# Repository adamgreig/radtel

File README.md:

# RadTel

This is a simple radio telemetry module using an STM32F0 microcontroller and an 
Si4460 radio transceiver. The board is designed to be used as part of a KiCAD 
tutorial workshop demonstrating basic circuit design, schematic capture, and 
PCB layout.

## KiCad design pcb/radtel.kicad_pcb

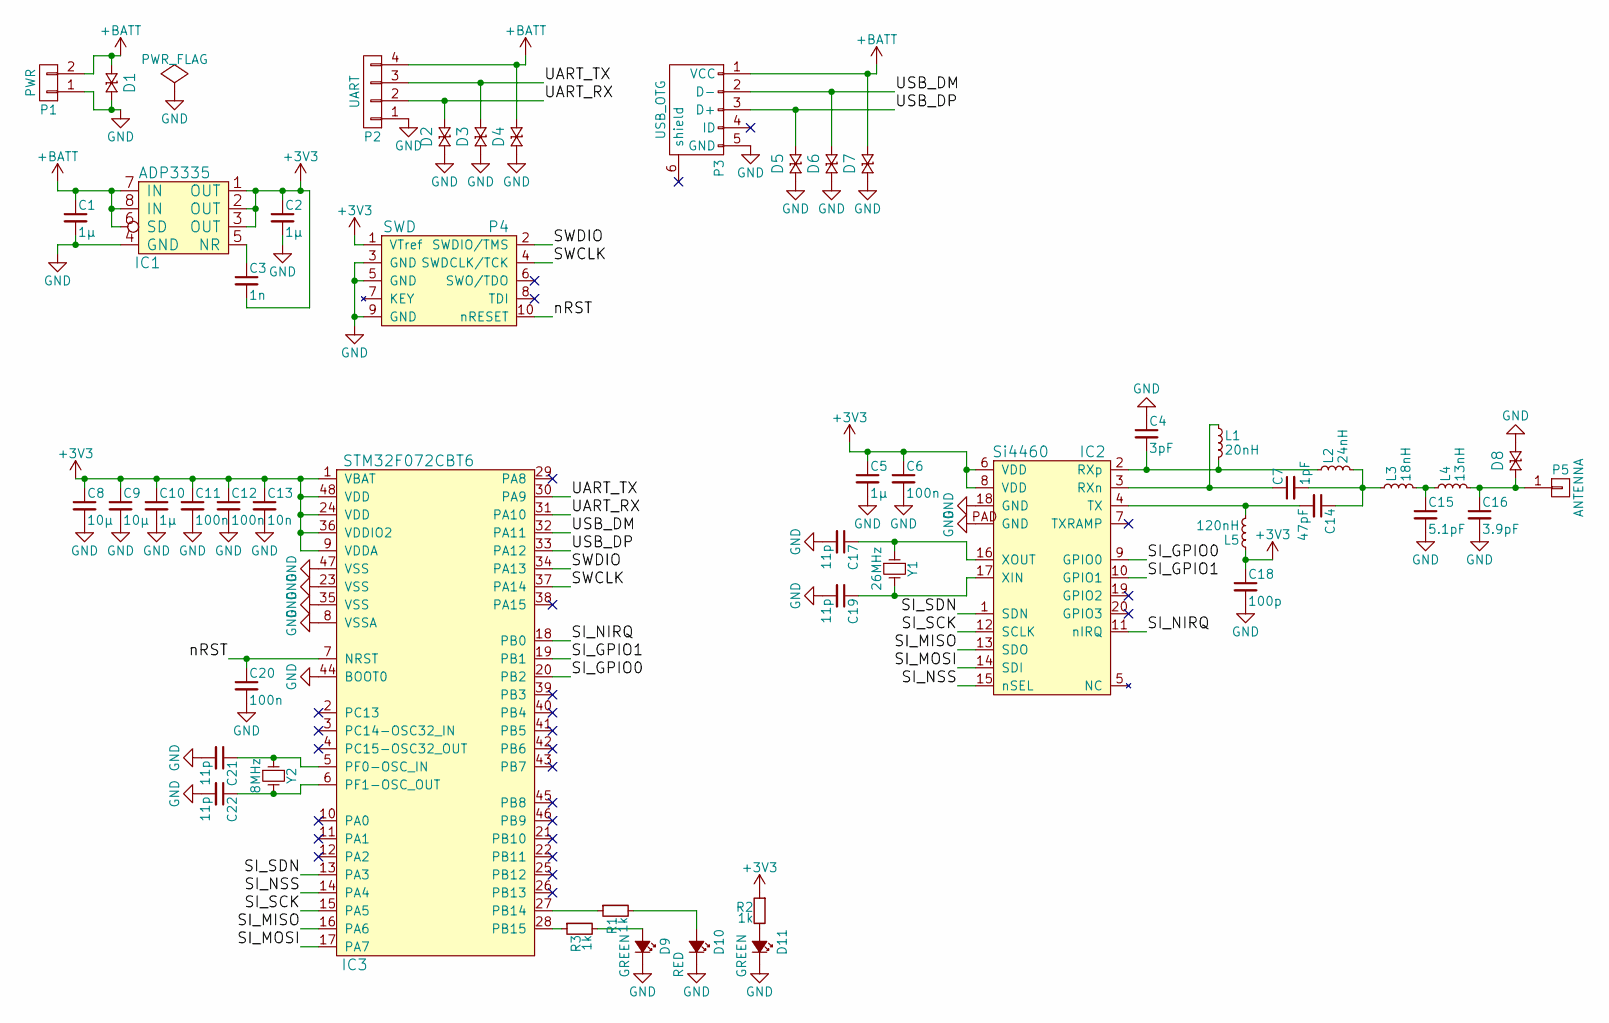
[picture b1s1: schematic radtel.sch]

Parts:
C1, C2, C5, C10: 1µ; C0603
C3: 1n; C0603
C4: 3pF; C0603
C6, C11, C12, C20: 100n; C0603
C7: 1pF; C0603
C8, C9: 10µ; C0603
C13: 10n; C0603
C14: 47pF; C0603
C15: 5.1pF; C0603
C16: 3.9pF; C0603
C17, C19, C21, C22: 11p; C0603
C18: 100p; C0603
D1, D2, D3, D4, D5, D6, D7, D8: CGA0402MLC-12G; R0603
D9, D11: GREEN; LED0603
D10: RED; LED0603
IC1: ADP3335; MSOP8
IC2: Si4460
IC3: STM32F072CBT6; LQFP48
L1: 20nH; L0603
L2: 24nH; L0603
L3: 18nH; L0603
L4: 13nH; L0603
L5: 120nH; L0603
P1: PWR; S02B-PASK-2
P2: UART; S04B-PASK-2
P3: USB_OTG; USB3065
P4: SWD; FTSH-105-01-F-D-K
P5: ANTENNA; WHIPANT
R1, R2, R3: 1k; R0603
Y1: 26MHz; XTAL50x32
Y2: 8MHz; XTAL50x32

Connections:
+3V3: C2.1, C3.2, C5.1, C6.1, C8.1, C9.1, C10.1, C11.1, C12.1, C13.1, C18.1, IC1.1 (OUT), IC1.2 (OUT), IC1.3 (OUT), IC2.6 (VDD), IC2.8 (VDD), IC3.1 (VBAT), IC3.9 (VDDA), IC3.24 (VDD), IC3.36 (VDDIO2), IC3.48 (VDD), L5.1, P4.1 (VTref), R2.1
+BATT: C1.1, D1.2, D4.1, D7.1, IC1.6 (SD), IC1.7 (IN), IC1.8 (IN), P1.2, P2.4, P3.1 (VCC)
/SI_GPIO0: IC2.9 (GPIO0), IC3.20 (PB2)
/SI_GPIO1: IC2.10 (GPIO1), IC3.19 (PB1)
/SI_MISO: IC2.13 (SDO), IC3.16 (PA6)
/SI_MOSI: IC2.14 (SDI), IC3.17 (PA7)
/SI_NIRQ: IC2.11 (nIRQ), IC3.18 (PB0)
/SI_NSS: IC2.15 (nSEL), IC3.14 (PA4)
/SI_SCK: IC2.12 (SCLK), IC3.15 (PA5)
/SI_SDN: IC2.1 (SDN), IC3.13 (PA3)
/SWCLK: IC3.37 (PA14), P4.4 (SWDCLK/TCK)
/SWDIO: IC3.34 (PA13), P4.2 (SWDIO/TMS)
/UART_RX: D2.1, IC3.31 (PA10), P2.2
/UART_TX: D3.1, IC3.30 (PA9), P2.3
/USB_DM: D6.1, IC3.32 (PA11), P3.2 (D-)
/USB_DP: D5.1, IC3.33 (PA12), P3.3 (D+)
/nRST: C20.1, IC3.7 (NRST), P4.10 (nRESET)
GND: C1.2, C2.2, C4.1, C5.2, C6.2, C8.2, C9.2, C10.2, C11.2, C12.2, C13.2, C15.2, C16.2, C17.2, C18.2, C19.2, C20.2, C21.2, C22.2, D1.1, D2.2, D3.2, D4.2, D5.2, D6.2, D7.2, D8.1, D9.1 (K), D10.1 (K), D11.1 (K), IC1.4 (GND), IC2.18 (GND), IC2.PAD (GND), IC3.8 (VSSA), IC3.23 (VSS), IC3.35 (VSS), IC3.44 (BOOT0), IC3.47 (VSS), P1.1, P2.1, P3.5 (GND), P4.3 (GND), P4.5 (GND), P4.9 (GND)
unnamed: C3.1, IC1.5 (NR)
unnamed: C4.2, IC2.2 (RXp), L1.2, L2.1
unnamed: C7.1, IC2.3 (RXn), L1.1
unnamed: C7.2, C14.1, L2.2, L3.1
unnamed: C14.2, IC2.4 (TX), L5.2
unnamed: C15.1, L3.2, L4.1
unnamed: C16.1, D8.2, L4.2, P5.1
unnamed: C17.1, IC2.16 (XOUT), Y1.1
unnamed: C19.1, IC2.17 (XIN), Y1.2
unnamed: C21.1, IC3.5 (PF0-OSC_IN), Y2.1
unnamed: C22.1, IC3.6 (PF1-OSC_OUT), Y2.2
unnamed: D9.2 (A), R3.2
unnamed: D10.2 (A), R1.2
unnamed: D11.2 (A), R2.2
unnamed: IC3.27 (PB14), R1.1
unnamed: IC3.28 (PB15), R3.1

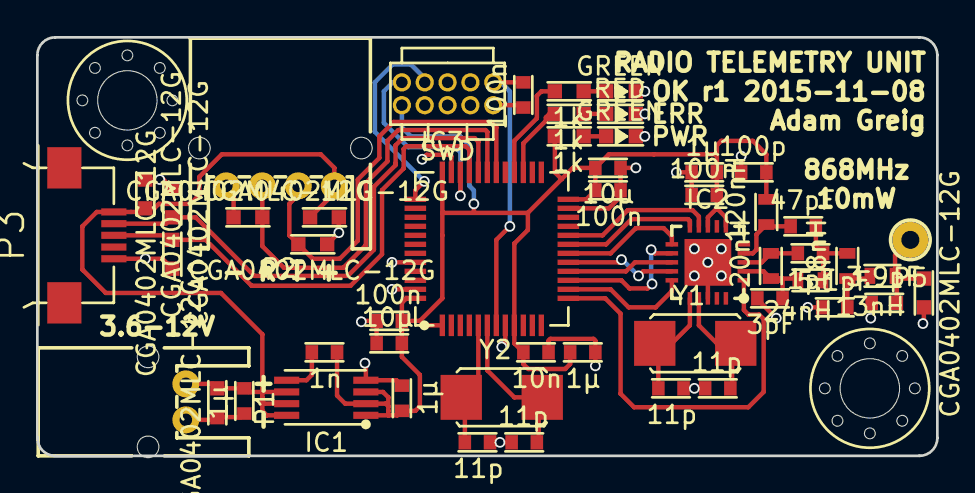
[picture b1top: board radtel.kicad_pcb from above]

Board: 2 copper layers, 50.0 x 23.2 mm, 53 parts (0 on the bottom side), 34 nets.

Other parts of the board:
M3_MOUNT, M3_MOUNT#2: VAL**; M3_MOUNT

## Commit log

2015-11-08 Initial commit. First revision of board; complete.
2015-11-09 move some capacitors a bit
2015-11-09 remove caps on radio xtal as not needed
2015-11-09 add farnell numbers
2015-11-09 add some example routed PCBs
